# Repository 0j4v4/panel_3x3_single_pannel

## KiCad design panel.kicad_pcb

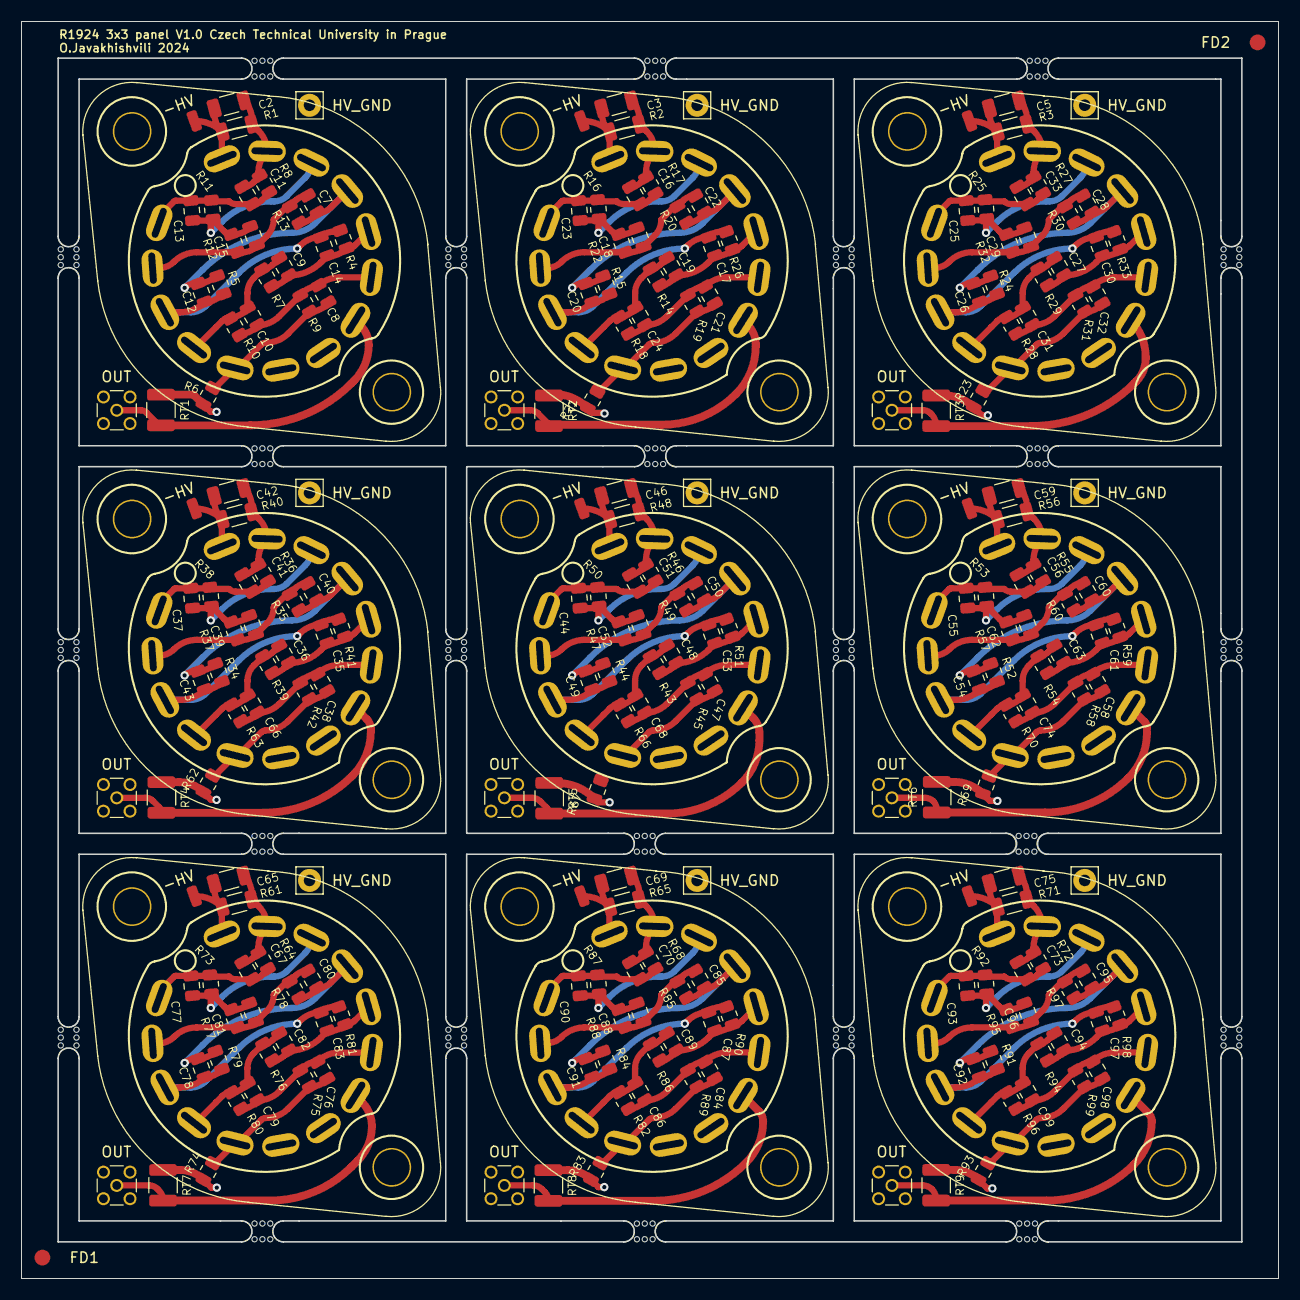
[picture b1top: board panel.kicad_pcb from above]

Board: 2 copper layers, 120.0 x 120.0 mm, 260 parts (0 on the bottom side), 103 nets.

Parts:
-HV: SolderWirePad_1x01_SMD_1x2mm
-HV#2, -HV#3, -HV#4, -HV#5, -HV#6, -HV#7, -HV#8, -HV#9: SolderWirePad_1x01_SMD_1x2mm
C2, C3, C5, C42, C46, C59, C65, C69, C75: 47p; C_1206_3216Metric
C7, C11, C12, C13, C14, C15, C16, C17, C18, C20, C22, C23, C25, C26, C28, C29, C30, C33, C35, C37, C39, C40, C41, C43, C44, C49, C50, C51, C52, C53, C54, C55, C56, C60, C61, C62, C67, C70, C73, C77, C78, C80, C81, C83, C85, C87, C88, C90, C91, C92, C93, C95, C96, C97: 47p; C_0805_2012Metric
C8, C9, C10, C19, C21, C24, C27, C31, C32, C36, C38, C47, C48, C58, C63, C66, C68, C74, C76, C79, C82, C84, C86, C89, C94, C98, C99: 10n; C_0805_2012Metric
FD1, FD2: Fiducial_1.5mm_Mask3mm
HV_GND: Pin_D1.1mm_L8.5mm_W2.5mm_FlatFork
HV_GND#2, HV_GND#3, HV_GND#4, HV_GND#5, HV_GND#6, HV_GND#7, HV_GND#8, HV_GND#9: Pin_D1.1mm_L8.5mm_W2.5mm_FlatFork
OUT: MMCX_Molex_73415-1471_Vertical
OUT#2, OUT#3, OUT#4, OUT#5, OUT#6, OUT#7, OUT#8, OUT#9: MMCX_Molex_73415-1471_Vertical
R1, R2, R3, R40, R48, R56, R61, R65, R71: 990k; R_1206_3216Metric
R4, R5, R6, R7, R8, R9, R10, R11, R12, R13, R14, R15, R16, R17, R18, R19, R20, R21, R22, R23, R24, R25, R26, R27, R28, R29, R30, R31, R32, R33, R34, R35, R36, R37, R38, R39, R41, R42, R43, R44, R45, R46, R47, R49, R50, R51, R52, R53, R54, R55, R57, R58, R59, R60, R62, R63, R64, R66, R67, R68, R69, R70, R72, R73, R74, R75, R76, R77, R78, R79, R80, R81, R82, R83, R84, R85, R86, R87, R88, R89, R90, R91, R92, R93, R94, R95, R96, R97, R98, R99: 330k; R_0805_2012Metric
RT1, RT2, RT3, RT4, RT5, RT6, RT7, RT8, RT9: 50; R_1210_3225Metric
U1x1, U1x2, U1x3, U2x1, U2x2, U2x3, U3x1, U3x2, U3x3: E2924
mouse-bite-2mm-slot, mouse-bite-2mm-slot#2, mouse-bite-2mm-slot#3, mouse-bite-2mm-slot#4, mouse-bite-2mm-slot#5, mouse-bite-2mm-slot#6, mouse-bite-2mm-slot#7, mouse-bite-2mm-slot#8, mouse-bite-2mm-slot#9, mouse-bite-2mm-slot#10, mouse-bite-2mm-slot#11, mouse-bite-2mm-slot#12, mouse-bite-2mm-slot#13, mouse-bite-2mm-slot#14, mouse-bite-2mm-slot#15, mouse-bite-2mm-slot#16, mouse-bite-2mm-slot#17, mouse-bite-2mm-slot#18, mouse-bite-2mm-slot#19, mouse-bite-2mm-slot#20, mouse-bite-2mm-slot#21, mouse-bite-2mm-slot#22, mouse-bite-2mm-slot#23, mouse-bite-2mm-slot#24: VAL**; mouse-bite-2mm-slot

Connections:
Board_0--HV: -HV#2.1, -HV#4.1, -HV#6.1, C2.2, C3.2, C5.2, R1.2, R2.2, R3.2, U1x1.1 (K), U1x2.1 (K), U1x3.1 (K)
Board_0-GND: HV_GND.1, HV_GND#2.1, HV_GND#3.1, HV_GND#4.1, HV_GND#5.1, HV_GND#6.1, HV_GND#7.1, HV_GND#8.1, HV_GND#9.1, OUT.2, OUT#2.2, OUT#3.2, OUT#4.2, OUT#5.2, OUT#6.2, OUT#7.2, OUT#8.2, OUT#9.2, R6.1, R21.1, R23.1, R62.1, R67.1, R69.1, R74.1, R83.1, R93.1, RT1.1, RT2.1, RT3.1, RT4.1, RT5.1, RT6.2, RT7.1, RT8.1, RT9.1
Board_0-Net-(J1-In): OUT#6.1, RT1.2, U1x1.7 (A)
Board_0-Net-(U1-Dy1): C2.1, C11.2, R1.1, R8.2, U1x1.2 (Dy1)
Board_0-Net-(U1-Dy2): C11.1, C13.2, R8.1, R11.2, U1x1.14 (Dy2)
Board_0-Net-(U1-Dy3): C13.1, C15.2, R11.1, R12.2, U1x1.3 (Dy3)
Board_0-Net-(U1-Dy4): C7.2, C15.1, R12.1, R13.2, U1x1.13 (Dy4)
Board_0-Net-(U1-Dy5): C7.1, C12.2, R5.2, R13.1, U1x1.4 (Dy5)
Board_0-Net-(U1-Dy6): C12.1, C14.2, R4.2, R5.1, U1x1.12 (Dy6)
Board_0-Net-(U1-Dy7): C9.2, C14.1, R4.1, R7.2, U1x1.5 (Dy7)
Board_0-Net-(U1-Dy8): C9.1, C10.2, R7.1, R10.2, U1x1.11 (Dy8)
Board_0-Net-(U1-Dy9): C8.2, C10.1, R9.2, R10.1, U1x1.6 (Dy9)
Board_0-Net-(U1-Dy10): C8.1, R6.2, R9.1, U1x1.10 (Dy10)
Board_1--HV: -HV.1, -HV#7.1, -HV#8.1, C42.2, C46.2, C59.2, R40.2, R48.2, R56.2, U2x1.1 (K), U2x2.1 (K), U2x3.1 (K)
Board_1-Net-(J1-In): OUT#7.1, RT2.2, U1x2.7 (A)
Board_1-Net-(U1-Dy1): C3.1, C16.2, R2.1, R17.2, U1x2.2 (Dy1)
Board_1-Net-(U1-Dy2): C16.1, C23.2, R16.2, R17.1, U1x2.14 (Dy2)
Board_1-Net-(U1-Dy3): C18.2, C23.1, R16.1, R22.2, U1x2.3 (Dy3)
Board_1-Net-(U1-Dy4): C18.1, C22.2, R20.2, R22.1, U1x2.13 (Dy4)
Board_1-Net-(U1-Dy5): C20.2, C22.1, R15.2, R20.1, U1x2.4 (Dy5)
Board_1-Net-(U1-Dy6): C17.2, C20.1, R15.1, R26.2, U1x2.12 (Dy6)
Board_1-Net-(U1-Dy7): C17.1, C19.2, R14.2, R26.1, U1x2.5 (Dy7)
Board_1-Net-(U1-Dy8): C19.1, C24.2, R14.1, R18.2, U1x2.11 (Dy8)
Board_1-Net-(U1-Dy9): C21.2, C24.1, R18.1, R19.2, U1x2.6 (Dy9)
Board_1-Net-(U1-Dy10): C21.1, R19.1, R21.2, U1x2.10 (Dy10)
Board_2--HV: -HV#3.1, -HV#5.1, -HV#9.1, C65.2, C69.2, C75.2, R61.2, R65.2, R71.2, U3x1.1 (K), U3x2.1 (K), U3x3.1 (K)
Board_2-Net-(J1-In): OUT.1, RT3.2, U1x3.7 (A)
Board_2-Net-(U1-Dy1): C5.1, C33.2, R3.1, R27.2, U1x3.2 (Dy1)
Board_2-Net-(U1-Dy2): C25.2, C33.1, R25.2, R27.1, U1x3.14 (Dy2)
Board_2-Net-(U1-Dy3): C25.1, C29.2, R25.1, R32.2, U1x3.3 (Dy3)
Board_2-Net-(U1-Dy4): C28.2, C29.1, R30.2, R32.1, U1x3.13 (Dy4)
Board_2-Net-(U1-Dy5): C26.2, C28.1, R24.2, R30.1, U1x3.4 (Dy5)
Board_2-Net-(U1-Dy6): C26.1, C30.2, R24.1, R33.2, U1x3.12 (Dy6)
Board_2-Net-(U1-Dy7): C27.2, C30.1, R29.2, R33.1, U1x3.5 (Dy7)
Board_2-Net-(U1-Dy8): C27.1, C31.2, R28.2, R29.1, U1x3.11 (Dy8)
Board_2-Net-(U1-Dy9): C31.1, C32.2, R28.1, R31.2, U1x3.6 (Dy9)
Board_2-Net-(U1-Dy10): C32.1, R23.2, R31.1, U1x3.10 (Dy10)
Board_3-Net-(J1-In): OUT#8.1, RT4.2, U2x1.7 (A)
Board_3-Net-(U1-Dy1): C41.2, C42.1, R36.2, R40.1, U2x1.2 (Dy1)
Board_3-Net-(U1-Dy2): C37.2, C41.1, R36.1, R38.2, U2x1.14 (Dy2)
Board_3-Net-(U1-Dy3): C37.1, C39.2, R37.2, R38.1, U2x1.3 (Dy3)
Board_3-Net-(U1-Dy4): C39.1, C40.2, R35.2, R37.1, U2x1.13 (Dy4)
Board_3-Net-(U1-Dy5): C40.1, C43.2, R34.2, R35.1, U2x1.4 (Dy5)
Board_3-Net-(U1-Dy6): C35.2, C43.1, R34.1, R41.2, U2x1.12 (Dy6)
Board_3-Net-(U1-Dy7): C35.1, C36.2, R39.2, R41.1, U2x1.5 (Dy7)
Board_3-Net-(U1-Dy8): C36.1, C66.2, R39.1, R63.2, U2x1.11 (Dy8)
Board_3-Net-(U1-Dy9): C38.2, C66.1, R42.2, R63.1, U2x1.6 (Dy9)
Board_3-Net-(U1-Dy10): C38.1, R42.1, R62.2, U2x1.10 (Dy10)
Board_4-Net-(J1-In): OUT#2.1, RT5.2, U2x2.7 (A)
Board_4-Net-(U1-Dy1): C46.1, C51.2, R46.2, R48.1, U2x2.2 (Dy1)
Board_4-Net-(U1-Dy2): C44.2, C51.1, R46.1, R50.2, U2x2.14 (Dy2)
Board_4-Net-(U1-Dy3): C44.1, C52.2, R47.2, R50.1, U2x2.3 (Dy3)
Board_4-Net-(U1-Dy4): C50.2, C52.1, R47.1, R49.2, U2x2.13 (Dy4)
Board_4-Net-(U1-Dy5): C49.2, C50.1, R44.2, R49.1, U2x2.4 (Dy5)
Board_4-Net-(U1-Dy6): C49.1, C53.2, R44.1, R51.2, U2x2.12 (Dy6)
Board_4-Net-(U1-Dy7): C48.2, C53.1, R43.2, R51.1, U2x2.5 (Dy7)
Board_4-Net-(U1-Dy8): C48.1, C68.2, R43.1, R66.2, U2x2.11 (Dy8)
Board_4-Net-(U1-Dy9): C47.2, C68.1, R45.2, R66.1, U2x2.6 (Dy9)
Board_4-Net-(U1-Dy10): C47.1, R45.1, R67.2, U2x2.10 (Dy10)
Board_5-Net-(J1-In): OUT#5.1, RT6.1, U2x3.7 (A)
Board_5-Net-(U1-Dy1): C56.2, C59.1, R55.2, R56.1, U2x3.2 (Dy1)
Board_5-Net-(U1-Dy2): C55.2, C56.1, R53.2, R55.1, U2x3.14 (Dy2)
Board_5-Net-(U1-Dy3): C55.1, C62.2, R53.1, R57.2, U2x3.3 (Dy3)
Board_5-Net-(U1-Dy4): C60.2, C62.1, R57.1, R60.2, U2x3.13 (Dy4)
Board_5-Net-(U1-Dy5): C54.2, C60.1, R52.2, R60.1, U2x3.4 (Dy5)
Board_5-Net-(U1-Dy6): C54.1, C61.2, R52.1, R59.2, U2x3.12 (Dy6)
Board_5-Net-(U1-Dy7): C61.1, C63.2, R54.2, R59.1, U2x3.5 (Dy7)
Board_5-Net-(U1-Dy8): C63.1, C74.2, R54.1, R70.2, U2x3.11 (Dy8)
Board_5-Net-(U1-Dy9): C58.2, C74.1, R58.2, R70.1, U2x3.6 (Dy9)
Board_5-Net-(U1-Dy10): C58.1, R58.1, R69.2, U2x3.10 (Dy10)
Board_6-Net-(J1-In): OUT#4.1, RT7.2, U3x1.7 (A)
Board_6-Net-(U1-Dy1): C65.1, C67.2, R61.1, R64.2, U3x1.2 (Dy1)
Board_6-Net-(U1-Dy2): C67.1, C77.2, R64.1, R73.2, U3x1.14 (Dy2)
Board_6-Net-(U1-Dy3): C77.1, C81.2, R73.1, R77.2, U3x1.3 (Dy3)
Board_6-Net-(U1-Dy4): C80.2, C81.1, R77.1, R78.2, U3x1.13 (Dy4)
Board_6-Net-(U1-Dy5): C78.2, C80.1, R78.1, R79.2, U3x1.4 (Dy5)
Board_6-Net-(U1-Dy6): C78.1, C83.2, R79.1, R81.2, U3x1.12 (Dy6)
Board_6-Net-(U1-Dy7): C82.2, C83.1, R76.2, R81.1, U3x1.5 (Dy7)
Board_6-Net-(U1-Dy8): C79.2, C82.1, R76.1, R80.2, U3x1.11 (Dy8)
Board_6-Net-(U1-Dy9): C76.2, C79.1, R75.2, R80.1, U3x1.6 (Dy9)
Board_6-Net-(U1-Dy10): C76.1, R74.2, R75.1, U3x1.10 (Dy10)
Board_7-Net-(J1-In): OUT#9.1, RT8.2, U3x2.7 (A)
Board_7-Net-(U1-Dy1): C69.1, C70.2, R65.1, R68.2, U3x2.2 (Dy1)
Board_7-Net-(U1-Dy2): C70.1, C90.2, R68.1, R87.2, U3x2.14 (Dy2)
Board_7-Net-(U1-Dy3): C88.2, C90.1, R87.1, R88.2, U3x2.3 (Dy3)
Board_7-Net-(U1-Dy4): C85.2, C88.1, R85.2, R88.1, U3x2.13 (Dy4)
Board_7-Net-(U1-Dy5): C85.1, C91.2, R84.2, R85.1, U3x2.4 (Dy5)
Board_7-Net-(U1-Dy6): C87.2, C91.1, R84.1, R90.2, U3x2.12 (Dy6)
Board_7-Net-(U1-Dy7): C87.1, C89.2, R86.2, R90.1, U3x2.5 (Dy7)
Board_7-Net-(U1-Dy8): C86.2, C89.1, R82.2, R86.1, U3x2.11 (Dy8)
Board_7-Net-(U1-Dy9): C84.2, C86.1, R82.1, R89.2, U3x2.6 (Dy9)
Board_7-Net-(U1-Dy10): C84.1, R83.2, R89.1, U3x2.10 (Dy10)
Board_8-Net-(J1-In): OUT#3.1, RT9.2, U3x3.7 (A)
Board_8-Net-(U1-Dy1): C73.2, C75.1, R71.1, R72.2, U3x3.2 (Dy1)
Board_8-Net-(U1-Dy2): C73.1, C93.2, R72.1, R92.2, U3x3.14 (Dy2)
Board_8-Net-(U1-Dy3): C93.1, C96.2, R92.1, R95.2, U3x3.3 (Dy3)
Board_8-Net-(U1-Dy4): C95.2, C96.1, R95.1, R97.2, U3x3.13 (Dy4)
Board_8-Net-(U1-Dy5): C92.2, C95.1, R91.2, R97.1, U3x3.4 (Dy5)
Board_8-Net-(U1-Dy6): C92.1, C97.2, R91.1, R98.2, U3x3.12 (Dy6)
Board_8-Net-(U1-Dy7): C94.2, C97.1, R94.2, R98.1, U3x3.5 (Dy7)
Board_8-Net-(U1-Dy8): C94.1, C99.2, R94.1, R96.2, U3x3.11 (Dy8)
Board_8-Net-(U1-Dy9): C98.2, C99.1, R96.1, R99.2, U3x3.6 (Dy9)
Board_8-Net-(U1-Dy10): C98.1, R93.2, R99.1, U3x3.10 (Dy10)

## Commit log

2025-03-25 initial upload
